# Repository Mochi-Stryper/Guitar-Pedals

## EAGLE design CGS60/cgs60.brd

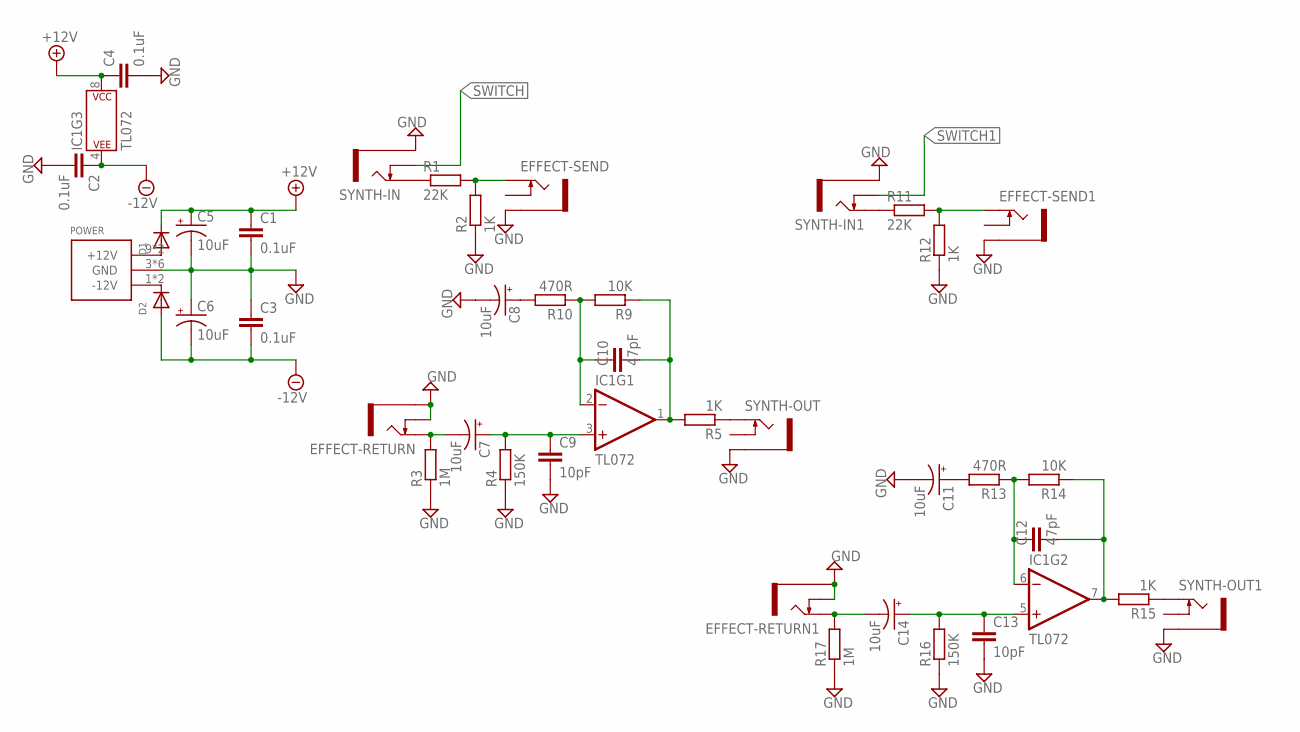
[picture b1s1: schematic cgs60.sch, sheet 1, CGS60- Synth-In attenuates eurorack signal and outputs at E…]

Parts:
C1, C2, C3, C4: 0.1uF; 0603
C5, C6, C7, C8, C11, C14: 10uF; PAN_B_SMD+THRU
C9, C13: 10pF; C0603
C10, C12: 47pF; C0603
D1, D2: DIODESOD-123; SOD-123
EFFECT-RETURN, EFFECT-RETURN1: THONKICONNNEW; WQP-PJ301M-12_JACK
EFFECT-SEND, EFFECT-SEND1: THONKICONNNEW; WQP-PJ301M-12_JACK
IC1: TL072; SO08
POWER: POWER_SIMPLE10; POWER_10
R1, R11: 22K; R0603
R2, R5, R12, R15: 1K; R0603
R3, R17: 1M; R0603
R4, R16: 150K; R0603
R9, R14: 10K; R0603
R10, R13: 470R; R0603
SYNTH-IN, SYNTH-IN1: THONKICONNNEW; WQP-PJ301M-12_JACK
SYNTH-OUT, SYNTH-OUT1: THONKICONNNEW; WQP-PJ301M-12_JACK

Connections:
+12V: C1.1, C4.1, C5.+, C5.++ (+), D1.C, IC1.8 (P$V+)
-12V: C2.1, C3.2, C6.-, C6.-- (-), D2.A, IC1.4 (P$V-)
GND: C1.2, C2.2, C3.1, C4.2, C5.-, C5.-- (-), C6.+, C6.++ (+), C8.-, C8.-- (-), C9.2, C11.-, C11.-- (-), C13.2, EFFECT-RETURN.P$2_SWITCH (SWITCH), EFFECT-RETURN.P$3_SLEEVE (SLEEVE), EFFECT-RETURN1.P$2_SWITCH (SWITCH), EFFECT-RETURN1.P$3_SLEEVE (SLEEVE), EFFECT-SEND.P$3_SLEEVE (SLEEVE), EFFECT-SEND1.P$3_SLEEVE (SLEEVE), POWER.3 (GND), POWER.4 (GND), POWER.5 (GND), POWER.6 (GND), POWER.7 (GND), POWER.8 (GND), R2.1, R3.1, R4.1, R12.1, R16.1, R17.1, SYNTH-IN.P$3_SLEEVE (SLEEVE), SYNTH-IN1.P$3_SLEEVE (SLEEVE), SYNTH-OUT.P$3_SLEEVE (SLEEVE), SYNTH-OUT1.P$3_SLEEVE (SLEEVE); also elsewhere on the board
unnamed: R1.1, SYNTH-IN.P$1_TIP (TIP)
unnamed: EFFECT-SEND.P$1_TIP (TIP), R1.2, R2.2
unnamed: C10.2, IC1.1 (OUT), R5.2, R9.1
unnamed: D1.A, POWER.9 (+12V), POWER.10 (+12V)
unnamed: C10.1, IC1.2 (-IN), R9.2, R10.1
unnamed: C8.+, C8.++ (+), R10.2
unnamed: C7.+, C7.++ (+), C9.1, IC1.3 (+IN), R4.2
unnamed: C7.-, C7.-- (-), EFFECT-RETURN.P$1_TIP (TIP), R3.2
unnamed: R5.1, SYNTH-OUT.P$1_TIP (TIP)
unnamed: R11.1, SYNTH-IN1.P$1_TIP (TIP)
unnamed: EFFECT-SEND1.P$1_TIP (TIP), R11.2, R12.2
unnamed: C11.+, C11.++ (+), R13.2
unnamed: C12.2, IC1.7 (OUT), R14.1, R15.2
unnamed: R15.1, SYNTH-OUT1.P$1_TIP (TIP)
unnamed: C14.-, C14.-- (-), EFFECT-RETURN1.P$1_TIP (TIP), R17.2
unnamed: C12.1, IC1.6 (-IN), R13.1, R14.2
unnamed: C13.1, C14.+, C14.++ (+), IC1.5 (+IN), R16.2
unnamed: D2.C, POWER.1 (-12V), POWER.2 (-12V)
SWITCH: SYNTH-IN.P$2_SWITCH (SWITCH); also elsewhere on the board
SWITCH1: SYNTH-IN1.P$2_SWITCH (SWITCH); also elsewhere on the board

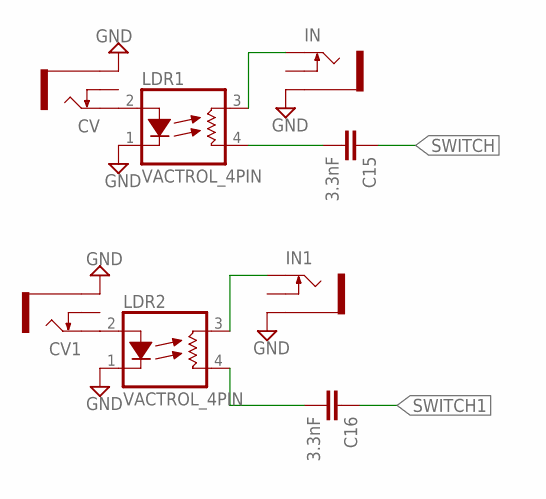
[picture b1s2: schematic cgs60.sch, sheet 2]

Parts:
C15, C16: 3.3nF; 0603
CV, CV1: THONKICONNNEW; WQP-PJ301M-12_JACK
IN, IN1: THONKICONNNEW; WQP-PJ301M-12_JACK
LDR1, LDR2: VACTROL_4PIN; VACTROL_4PIN_VTL5C

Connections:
GND: CV.P$3_SLEEVE (SLEEVE), CV1.P$3_SLEEVE (SLEEVE), IN.P$3_SLEEVE (SLEEVE), IN1.P$3_SLEEVE (SLEEVE), LDR1.1 (LED-), LDR2.1 (LED-); also elsewhere on the board
unnamed: CV.P$1_TIP (TIP), LDR1.2 (LED+)
unnamed: IN.P$1_TIP (TIP), LDR1.3 (RES1)
unnamed: C15.2, LDR1.4 (RES2)
unnamed: CV1.P$1_TIP (TIP), LDR2.2 (LED+)
unnamed: IN1.P$1_TIP (TIP), LDR2.3 (RES1)
unnamed: C16.2, LDR2.4 (RES2)
SWITCH: C15.1; also elsewhere on the board
SWITCH1: C16.1; also elsewhere on the board

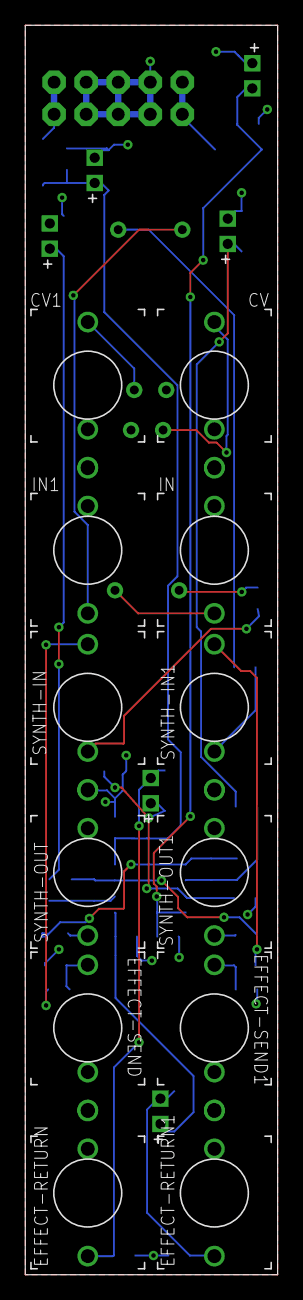
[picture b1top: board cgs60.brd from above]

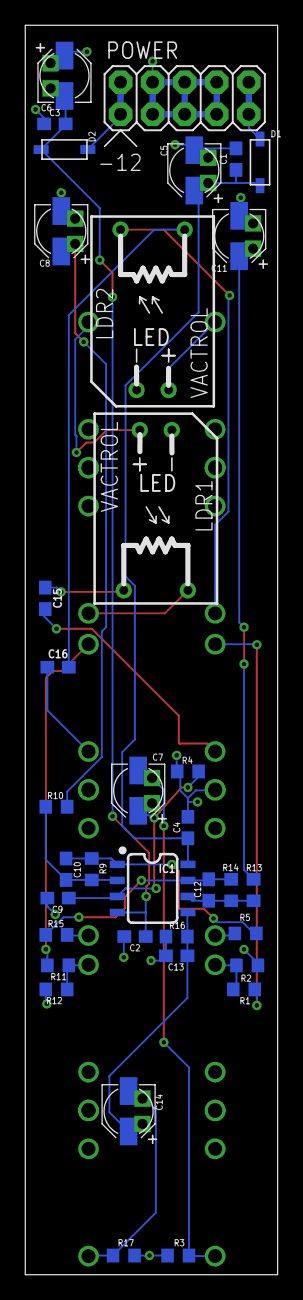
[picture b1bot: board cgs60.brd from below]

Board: 2 copper layers, 20.0 x 99.0 mm, 48 parts (36 on the bottom side), 29 nets.

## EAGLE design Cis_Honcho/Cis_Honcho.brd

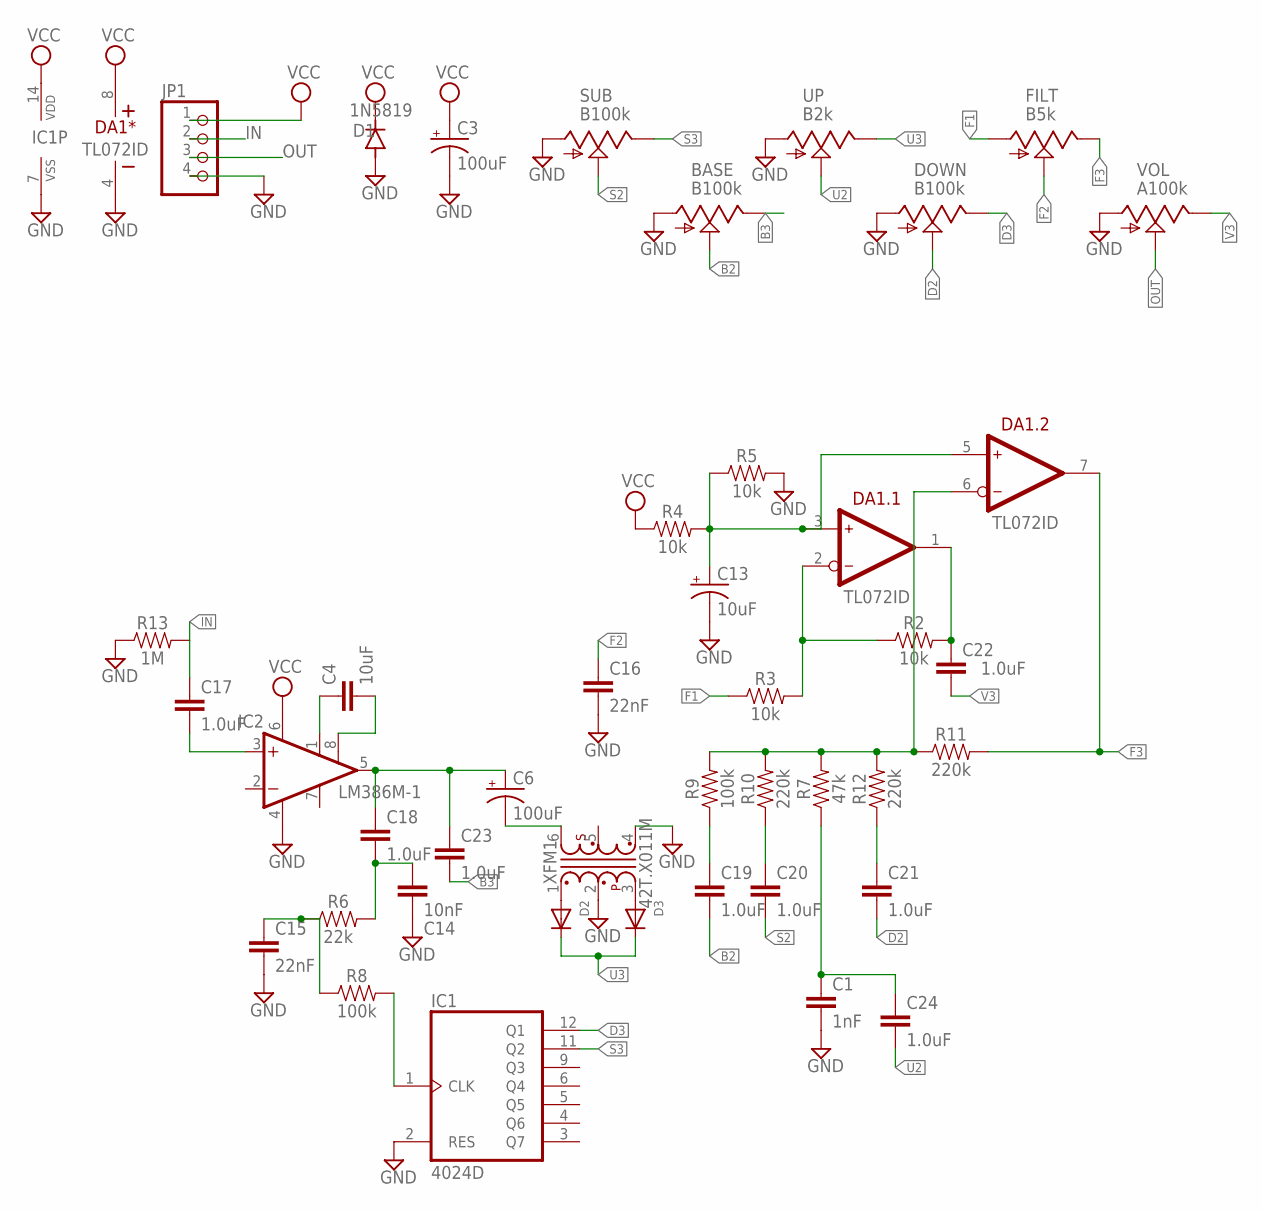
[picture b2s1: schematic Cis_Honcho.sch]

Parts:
BASE: B100k; 9MM_SNAP-IN_POT
C1: 1nF; 0603
C3, C6: 100uF; E2,5-6
C4: 10uF; 1210
C13: 10uF; PANASONIC_B
C14: 10nF; 0603
C15, C16: 22nF; 0603
C17, C18, C19, C20, C21, C22, C23, C24: 1.0uF; 0603
D1: 1N5819; SOD123
D2, D3: DIODESOD-123; SOD-123
DA1: TL072ID; SO-8
DOWN: B100k; 9MM_SNAP-IN_POT
FILT: B5k; 9MM_SNAP-IN_POT
IC1: 4024D; SO14
IC2: LM386M-1; SO08
JP1: PINHD-1X4; 1X04
R2, R3, R4, R5: 10k; 0603
R6: 22k; 0603
R7: 47k; 0603
R8, R9: 100k; 0603
R10, R11, R12: 220k; 0603
R13: 1M; 0603
SUB: B100k; 9MM_SNAP-IN_POT
UP: B2k; 9MM_SNAP-IN_POT
VOL: A100k; 9MM_SNAP-IN_POT
XFM1: 42T.X011M; 42TM

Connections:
B2: BASE.2 (S), C19.2
B3: BASE.3 (E), C23.2
D2: C21.2, DOWN.2 (S)
D3: DOWN.3 (E), IC1.12 (Q1)
F1: FILT.1 (A), R3.1
F2: C16.1, FILT.2 (S)
F3: DA1.7 (OUT), FILT.3 (E), R11.2
GND: BASE.1 (A), C1.2, C3.-, C13.-, C14.2, C15.2, C16.2, D1.A, DA1.4 (V-), DOWN.1 (A), IC1.2 (RES), IC1.7 (VSS), IC2.4 (GND), JP1.4, R5.2, R13.1, SUB.1 (A), UP.1 (A), VOL.1 (A), XFM1.2, XFM1.4
IN: C17.1, JP1.2, R13.2
unnamed: C17.2, IC2.3 (+IN)
unnamed: C4.1, IC2.1 (GAIN)
unnamed: C4.2, IC2.8 (GAIN)
unnamed: C6.+, C18.1, C23.1, IC2.5 (OUT)
unnamed: C14.1, C18.2, R6.2
unnamed: C15.1, R6.1, R8.1
unnamed: IC1.1 (CLK), R8.2
unnamed: C6.-, XFM1.6
unnamed: D2.A, XFM1.1
unnamed: D3.A, XFM1.3
unnamed: DA1.6 (IN-), R7.2, R9.2, R10.2, R11.1, R12.2
unnamed: C19.1, R9.1
unnamed: C20.1, R10.1
unnamed: C21.1, R12.1
unnamed: C1.1, C24.1, R7.1
unnamed: C13.+, DA1.3 (IN+), DA1.5 (IN+), R4.2, R5.1
unnamed: C22.1, DA1.1 (OUT), R2.2
unnamed: DA1.2 (IN-), R2.1, R3.2
OUT: JP1.3, VOL.2 (S)
S2: C20.2, SUB.2 (S)
S3: IC1.11 (Q2), SUB.3 (E)
U2: C24.2, UP.2 (S)
U3: D2.C, D3.C, UP.3 (E)
V3: C22.2, VOL.3 (E)
VCC: C3.+, D1.C, DA1.8 (V+), IC1.14 (VDD), IC2.6 (VS), JP1.1, R4.1

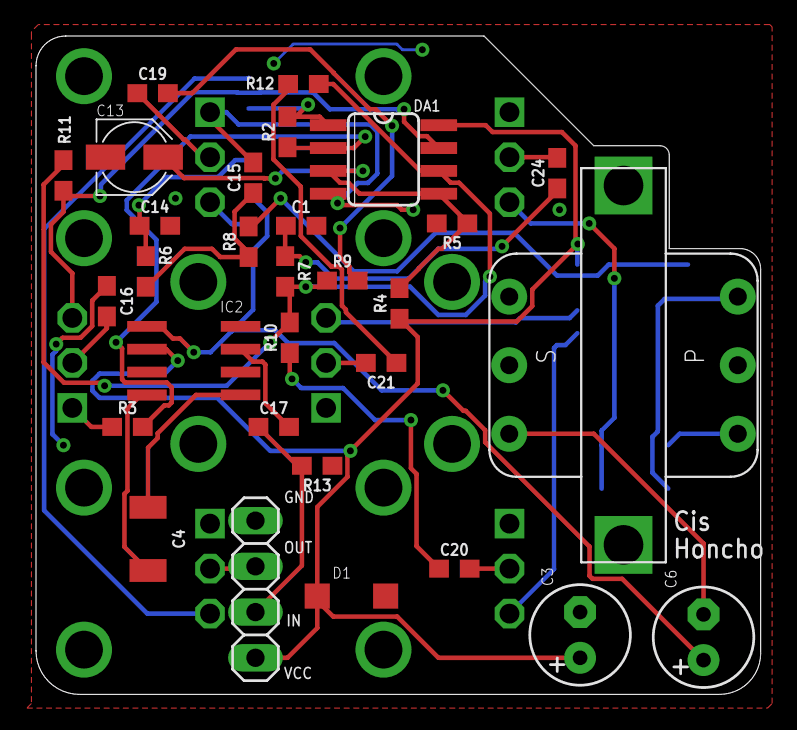
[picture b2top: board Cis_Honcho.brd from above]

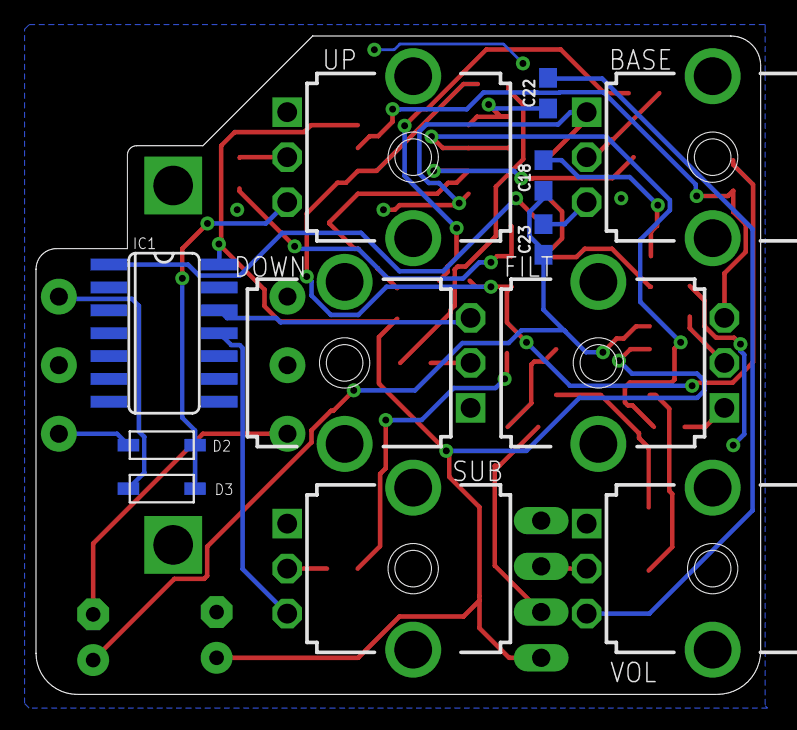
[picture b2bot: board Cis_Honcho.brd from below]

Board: 2 copper layers, 40.3 x 36.6 mm, 42 parts (12 on the bottom side), 34 nets.

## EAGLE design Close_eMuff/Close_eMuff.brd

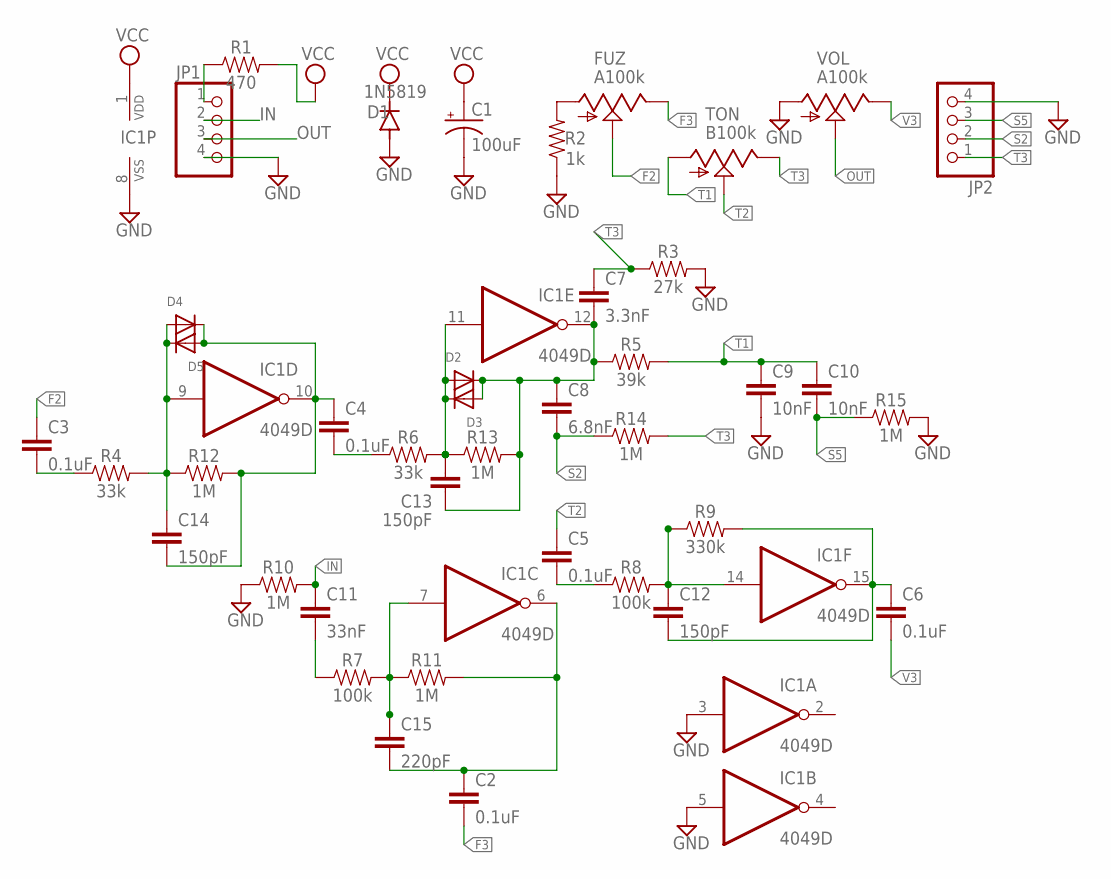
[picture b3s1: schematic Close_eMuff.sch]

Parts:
C1: 100uF; PAN_B_SMD+THRU
C2, C3, C4, C5, C6: 0.1uF; 0603
C7: 3.3nF; 0603
C8: 6.8nF; 0603
C9, C10: 10nF; 0603
C11: 33nF; 0603
C12, C13, C14: 150pF; 0603
C15: 220pF; 0603
D1: 1N5819; SOD123
D2, D3, D4, D5: DIODESOD-123; SOD-123
FUZ: A100k; 9MM_SNAP-IN_POT
IC1: 4049D; SO16
JP1, JP2: PINHD-1X4; 1X04
R1: 470; 0603
R2: 1k; 0603
R3: 27k; 0603
R4, R6: 33k; 0603
R5: 39k; 0603
R7, R8: 100k; 0603
R9: 330k; 0603
R10, R11, R12, R13, R14, R15: 1M; 0603
TON: B100k; 9MM_SNAP-IN_POT
VOL: A100k; 9MM_SNAP-IN_POT

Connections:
F2: C3.1, FUZ.2 (S)
F3: C2.2, FUZ.3 (E)
GND: C1.-, C1.-- (-), C9.2, D1.A, IC1.3 (I), IC1.5 (I), IC1.8 (VSS), JP1.4, JP2.4, R2.1, R3.2, R10.1, R15.2, VOL.1 (A)
IN: C11.1, JP1.2, R10.2
unnamed: C11.2, R7.1
unnamed: C15.1, IC1.7 (I), R7.2, R11.1
unnamed: FUZ.1 (A), R2.2
unnamed: C2.1, C15.2, IC1.6 (O), R11.2
unnamed: C3.2, R4.1
unnamed: C14.1, D4.A, D5.C, IC1.9 (I), R4.2, R12.1
unnamed: C4.2, R6.1
unnamed: C4.1, C14.2, D4.C, D5.A, IC1.10 (O), R12.2
unnamed: C13.1, D2.A, D3.C, IC1.11 (I), R6.2, R13.1
unnamed: JP1.1, R1.1
unnamed: C5.2, R8.1
unnamed: C7.2, C8.1, C13.2, D2.C, D3.A, IC1.12 (O), R5.1, R13.2
unnamed: C12.1, IC1.14 (I), R8.2, R9.1
unnamed: C6.1, C12.2, IC1.15 (O), R9.2
OUT: JP1.3, VOL.2 (S)
S2: C8.2, JP2.2, R14.1
S5: C10.2, JP2.3, R15.1
T1: C9.1, C10.1, R5.2, TON.1 (A)
T2: C5.1, TON.2 (S)
T3: C7.1, JP2.1, R3.1, R14.2, TON.3 (E)
V3: C6.2, VOL.3 (E)
VCC: C1.+, C1.++ (+), D1.C, IC1.1 (VDD), R1.2

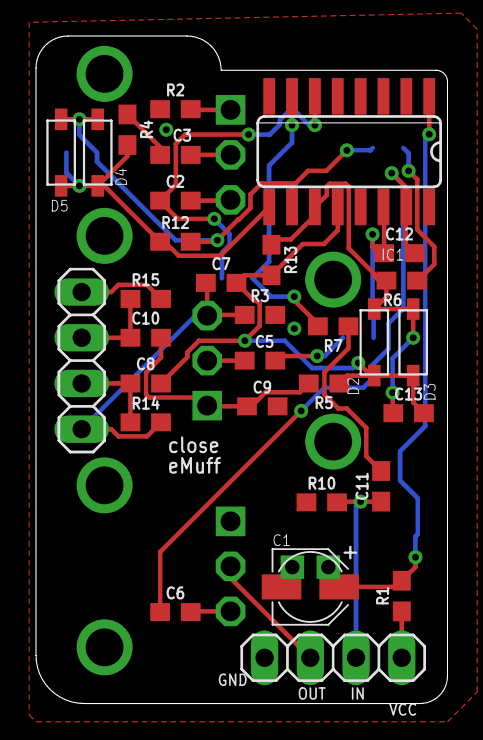
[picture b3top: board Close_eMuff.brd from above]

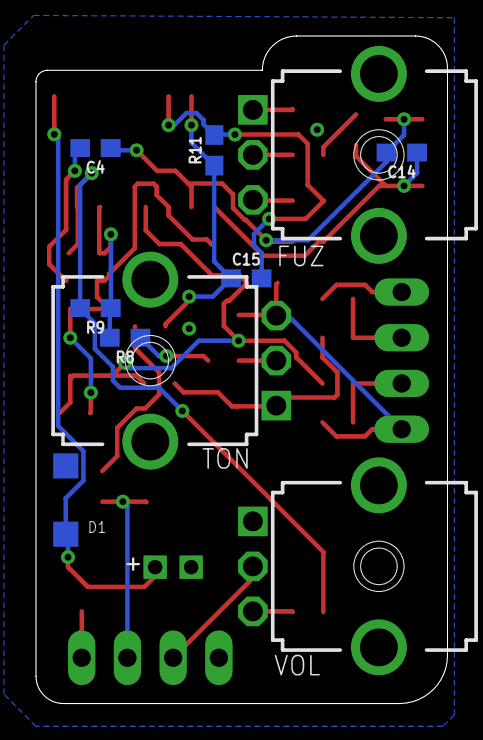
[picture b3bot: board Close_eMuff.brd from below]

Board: 2 copper layers, 22.9 x 37.1 mm, 41 parts (10 on the bottom side), 26 nets.

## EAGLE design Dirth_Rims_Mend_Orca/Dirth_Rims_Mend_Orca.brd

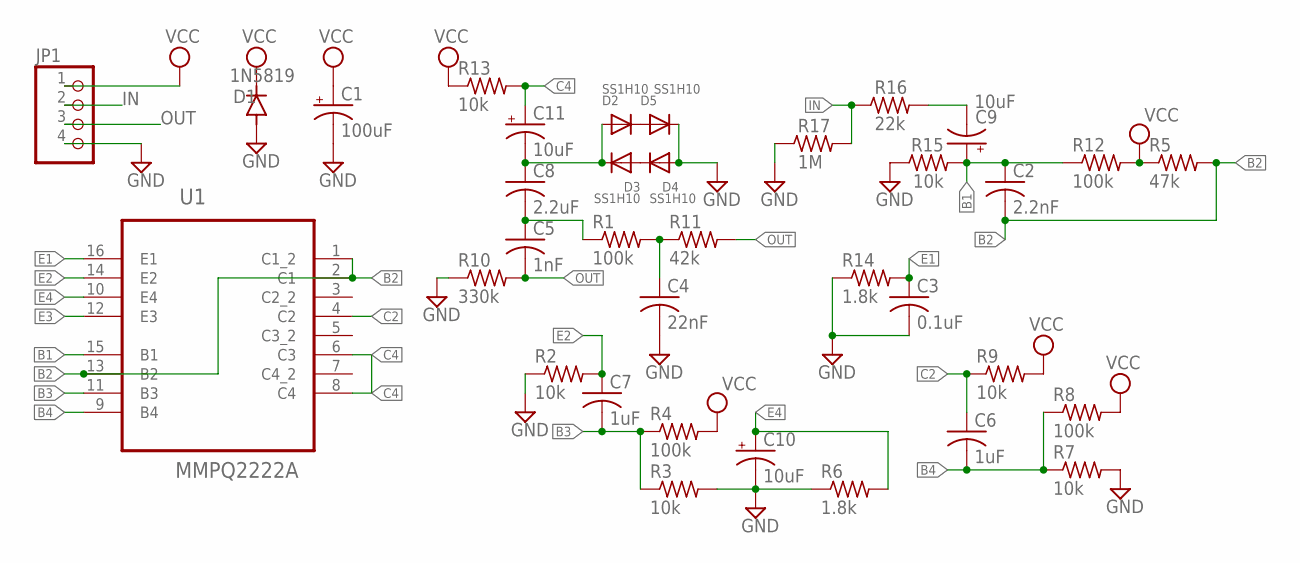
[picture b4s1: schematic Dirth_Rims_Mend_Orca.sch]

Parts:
C1: 100uF; PAN_B_SMD+THRU
C2: 2.2nF; C0603
C3: 0.1uF; C0603
C4: 22nF; C0603
C5: 1nF; C0603
C6, C7: 1uF; C0603
C8: 2.2uF; C0603
C9, C10, C11: 10uF; PAN_B_SMD+THRU
D1: 1N5819; SOD123
D2, D3, D4, D5: SS1H10; SMADIODE
JP1: PINHD-1X4; 1X04
R1, R4, R8, R12: 100k; R0603
R2, R3, R7, R9, R13, R15: 10k; R0603
R5: 47k; R0603
R6, R14: 1.8k; R0603
R10: 330k; R0603
R11: 42k; R0603
R16: 22k; R0603
R17: 1M; R0603
U1: MMPQ2222A; SOIC127P600X175-16N

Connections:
B1: C2.1, C9.+, C9.++ (+), R12.1, R15.2, U1.15 (B1)
B2: C2.2, R5.2, U1.1 (C1_2), U1.2 (C1), U1.13 (B2)
B3: C7.2, R3.1, R4.1, U1.11 (B3)
B4: C6.2, R7.1, R8.1, U1.9 (B4)
C2: C6.1, R9.1, U1.4 (C2)
C4: C11.+, C11.++ (+), R13.2, U1.6 (C3), U1.8 (C4)
E1: C3.1, R14.2, U1.16 (E1)
E2: C7.1, R2.2, U1.14 (E2)
E3: U1.12 (E3)
E4: C10.+, C10.++ (+), R6.2, U1.10 (E4)
GND: C1.-, C1.-- (-), C3.2, C4.2, C10.-, C10.-- (-), D1.A, D4.A, D5.C, JP1.4, R2.1, R3.2, R6.1, R7.2, R10.1, R14.1, R15.1, R17.1
IN: JP1.2, R16.1, R17.2
unnamed: C9.-, C9.-- (-), R16.2
unnamed: C8.1, C11.-, C11.-- (-), D2.A, D3.C
unnamed: C5.1, C8.2, R1.1
unnamed: D3.A, D4.C
unnamed: D2.C, D5.A
unnamed: C4.1, R1.2, R11.1
OUT: C5.2, JP1.3, R10.2, R11.2
VCC: C1.+, C1.++ (+), D1.C, JP1.1, R4.2, R5.1, R8.2, R9.2, R12.2, R13.1

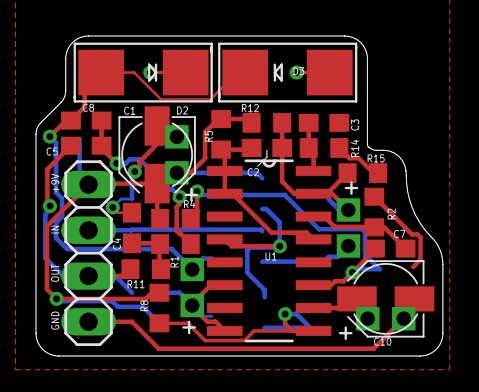
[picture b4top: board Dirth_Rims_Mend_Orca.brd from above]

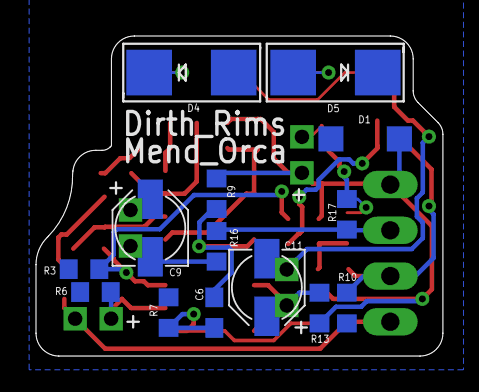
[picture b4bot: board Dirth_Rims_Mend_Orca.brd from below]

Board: 2 copper layers, 22.6 x 17.8 mm, 35 parts (14 on the bottom side), 19 nets.

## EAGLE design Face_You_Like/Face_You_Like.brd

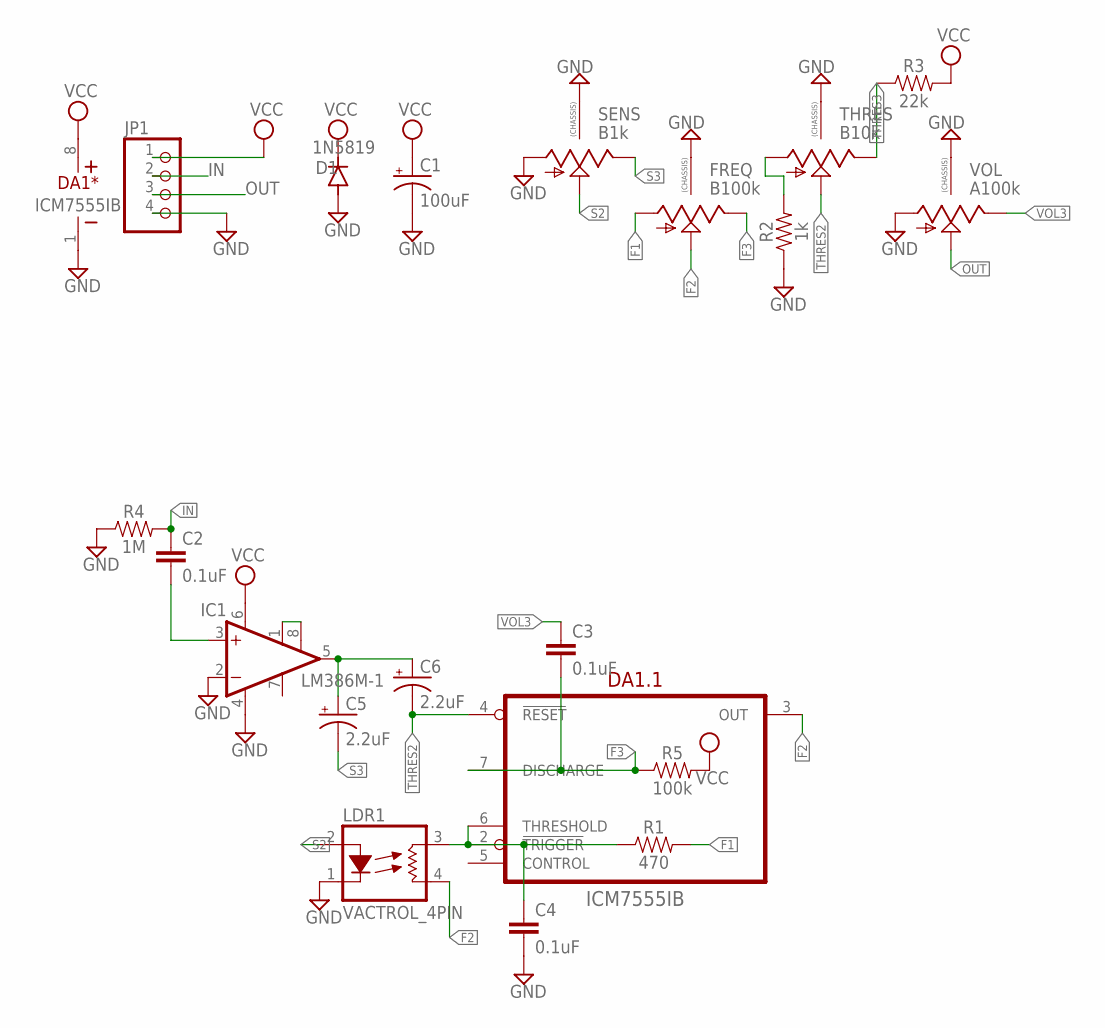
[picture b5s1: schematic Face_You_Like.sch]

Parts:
C1: 100uF; PAN_B_SMD+THRU
C2, C3, C4: 0.1uF; 0603
C5, C6: 2.2uF; PAN_B_SMD+THRU
D1: 1N5819; SOD123
DA1: ICM7555IB; SO-8
FREQ: B100k; 9MM_SNAP-IN_POT
IC1: LM386M-1; SO08
JP1: PINHD-1X4; 1X04
LDR1: VACTROL_4PIN; VACTROL_4PIN_VTL5C
R1: 470; 0603
R2: 1k; 0603
R3: 22k; 0603
R4: 1M; 0603
R5: 100k; 0603
SENS: B1k; 9MM_SNAP-IN_POT
THRES: B10k; 9MM_SNAP-IN_POT
VOL: A100k; 9MM_SNAP-IN_POT

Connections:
F1: FREQ.1 (A), R1.2
F2: DA1.3 (OUT), FREQ.2 (S), LDR1.4 (RES2)
F3: C3.2, DA1.7 (DISCHARGE), FREQ.3 (E), R5.1
GND: C1.-, C1.-- (-), C4.2, D1.A, DA1.1 (V-), FREQ.CHASSIS1, FREQ.CHASSIS2, IC1.2 (-IN), IC1.4 (GND), JP1.4, LDR1.1 (LED-), R2.1, R4.1, SENS.1 (A), SENS.CHASSIS1, SENS.CHASSIS2, THRES.CHASSIS1, THRES.CHASSIS2, VOL.1 (A), VOL.CHASSIS1, VOL.CHASSIS2
IN: C2.1, JP1.2, R4.2
unnamed: IC1.1 (GAIN), IC1.8 (GAIN)
unnamed: C2.2, IC1.3 (+IN)
unnamed: R2.2, THRES.1 (A)
unnamed: C5.+, C5.++ (+), C6.+, C6.++ (+), IC1.5 (OUT)
unnamed: C4.1, DA1.2 (!TRIGGER), DA1.6 (THRESHOLD), LDR1.3 (RES1), R1.1
OUT: JP1.3, VOL.2 (S)
S2: LDR1.2 (LED+), SENS.2 (S)
S3: C5.-, C5.-- (-), SENS.3 (E)
THRES2: C6.-, C6.-- (-), DA1.4 (!RESET), THRES.2 (S)
THRES3: R3.1, THRES.3 (E)
VCC: C1.+, C1.++ (+), D1.C, DA1.8 (V+), IC1.6 (VS), JP1.1, R3.2, R5.2
VOL3: C3.1, VOL.3 (E)

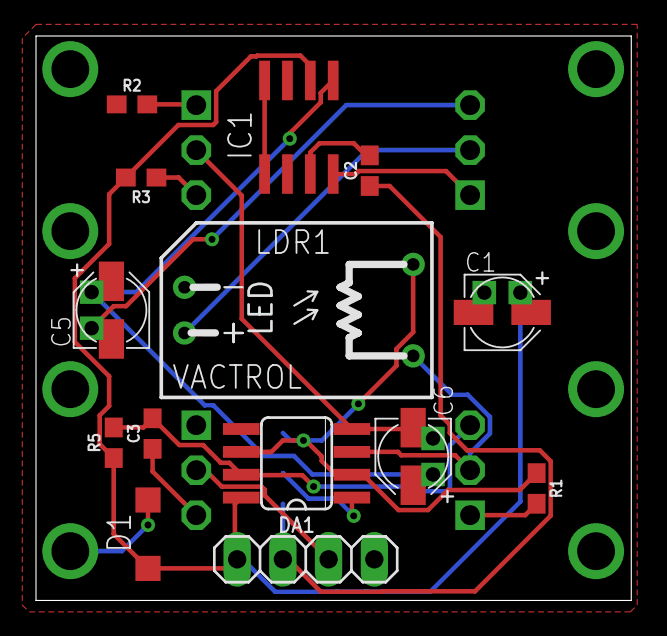
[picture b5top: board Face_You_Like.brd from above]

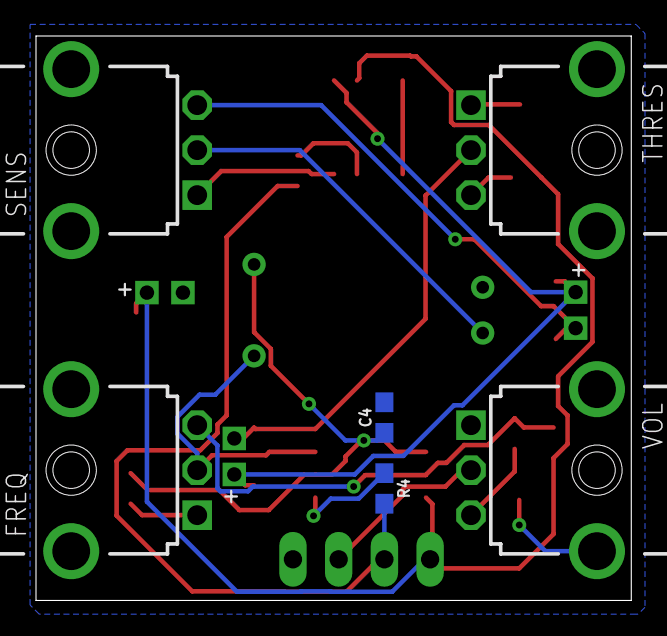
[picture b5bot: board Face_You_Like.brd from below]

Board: 2 copper layers, 33.1 x 31.4 mm, 20 parts (6 on the bottom side), 17 nets.

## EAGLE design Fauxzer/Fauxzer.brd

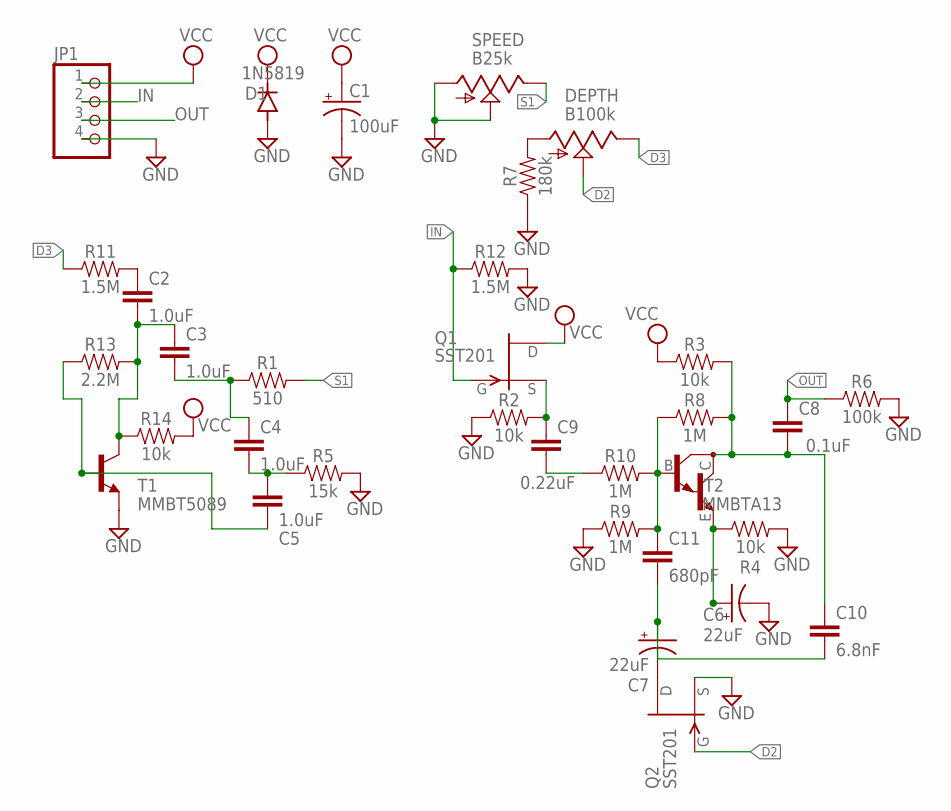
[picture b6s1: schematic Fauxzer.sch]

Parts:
C1: 100uF; PAN_B_SMD+THRU
C2, C3, C4, C5: 1.0uF; 0805
C6, C7: 22uF; PAN_B_SMD+THRU
C8: 0.1uF; 0603
C9: 0.22uF; 0603
C10: 6.8nF; 0603
C11: 680pF; 0603
D1: 1N5819; SOD123
DEPTH: B100k; 9MM_SNAP-IN_POT
JP1: PINHD-1X4; 1X04
Q1, Q2: SST201; SOT23
R1: 510; 0603
R2, R3, R4, R14: 10k; 0603
R5: 15k; 0603
R6: 100k; 0603
R7: 180k; 0603
R8, R9, R10: 1M; 0603
R11, R12: 1.5M; 0603
R13: 2.2M; 0603
SPEED: B25k; 9MM_SNAP-IN_POT
T1: MMBT5089; SOT23-BEC
T2: MMBTA13; SOT23-BEC

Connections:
D2: DEPTH.2 (S), Q2.3 (G)
D3: DEPTH.3 (E), R11.1
GND: C1.-, C1.-- (-), C6.-, C6.-- (-), D1.A, JP1.4, Q2.2 (S), R2.1, R4.2, R5.2, R6.2, R7.1, R9.1, R12.2, SPEED.1 (A), SPEED.2 (S), T1.E
IN: JP1.2, Q1.3 (G), R12.1
unnamed: C2.1, R11.2
unnamed: C9.1, Q1.2 (S), R2.2
unnamed: C9.2, R10.1
unnamed: C11.1, R8.1, R9.2, R10.2, T2.B
unnamed: C7.+, C7.++ (+), C10.2, C11.2
unnamed: C7.-, C7.-- (-), Q2.1 (D)
unnamed: C8.2, C10.1, R3.2, R8.2, T2.C
unnamed: C6.+, C6.++ (+), R4.1, T2.E
unnamed: DEPTH.1 (A), R7.2
unnamed: C3.2, C4.1, R1.1
unnamed: C2.2, C3.1, R13.2, R14.1, T1.C
unnamed: C5.2, R13.1, T1.B
unnamed: C4.2, C5.1, R5.1
OUT: C8.1, JP1.3, R6.1
S1: R1.2, SPEED.3 (E)
VCC: C1.+, C1.++ (+), D1.C, JP1.1, Q1.1 (D), R3.1, R14.2

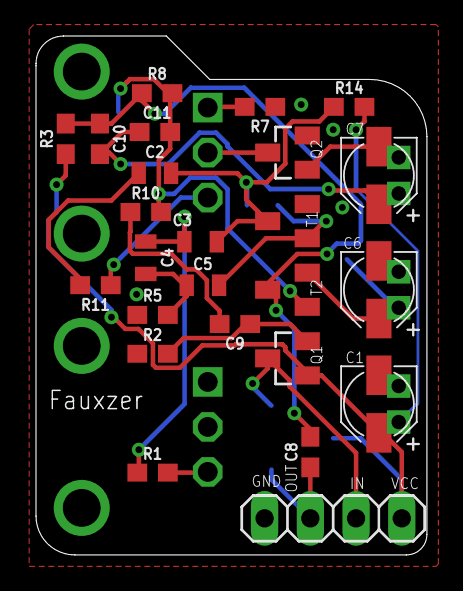
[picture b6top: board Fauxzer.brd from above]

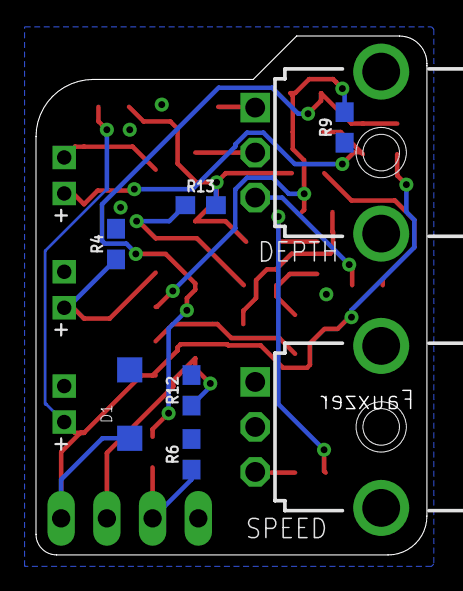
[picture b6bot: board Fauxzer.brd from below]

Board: 2 copper layers, 21.7 x 28.8 mm, 33 parts (8 on the bottom side), 20 nets.

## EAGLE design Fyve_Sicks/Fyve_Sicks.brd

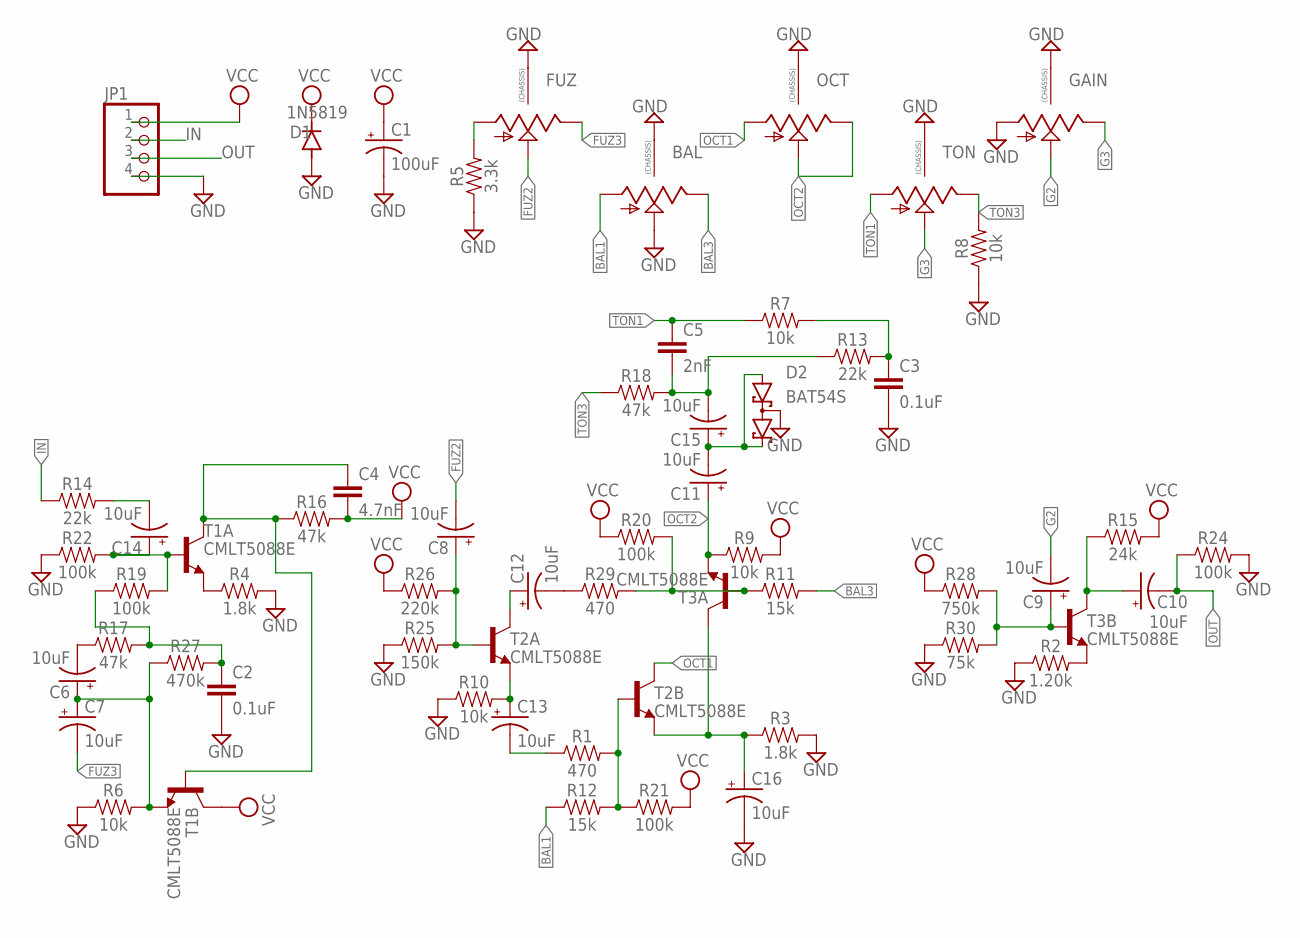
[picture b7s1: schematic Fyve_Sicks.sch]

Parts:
BAL: 9MM_SNAP-IN_POT_CHASSIS; 9MM_SNAP-IN_POT
C1: 100uF; PAN_B_SMD+THRU
C2, C3: 0.1uF; 0603
C4: 4.7nF; 0603
C5: 2nF; 0603
C6, C7, C8, C9, C10, C11, C12, C13, C14, C15, C16: 10uF; EIA3528
D1: 1N5819; SOD123
D2: BAT54S; SOT23
FUZ: 9MM_SNAP-IN_POT_CHASSIS; 9MM_SNAP-IN_POT
GAIN: 9MM_SNAP-IN_POT_CHASSIS; 9MM_SNAP-IN_POT
JP1: PINHD-1X4; 1X04
OCT: 9MM_SNAP-IN_POT_CHASSIS; 9MM_SNAP-IN_POT
R1, R29: 470; 0603
R2: 1.20k; 0603
R3, R4: 1.8k; 0603
R5: 3.3k; 0603
R6, R7, R8, R9, R10: 10k; 0603
R11, R12: 15k; 0603
R13, R14: 22k; 0603
R15: 24k; 0603
R16, R17, R18: 47k; 0603
R19, R20, R21, R22, R24: 100k; 0603
R25: 150k; 0603
R26: 220k; 0603
R27: 470k; 0603
R28: 750k; 0603
R30: 75k; 0603
T1, T2, T3: CMLT5088E; SOT563
TON: 9MM_SNAP-IN_POT_CHASSIS; 9MM_SNAP-IN_POT

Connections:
BAL1: BAL.1 (A), R12.1
BAL3: BAL.3 (E), R11.2
FUZ2: C8.C (-), FUZ.2 (S)
FUZ3: C7.C (-), FUZ.3 (E)
G2: C9.C (-), GAIN.2 (S)
G3: GAIN.3 (E), TON.2 (S)
GND: BAL.2 (S), BAL.CHASSIS1, BAL.CHASSIS2, C1.-, C1.-- (-), C2.2, C3.2, C16.C (-), D1.A, D2.3 (C1A2), FUZ.CHASSIS1, FUZ.CHASSIS2, GAIN.1 (A), GAIN.CHASSIS1, GAIN.CHASSIS2, JP1.4, OCT.CHASSIS1, OCT.CHASSIS2, R2.1, R3.2, R4.2, R5.1, R6.1, R8.1, R10.1, R22.1, R24.2, R25.1, R30.1, TON.CHASSIS1, TON.CHASSIS2
IN: JP1.2, R14.1
unnamed: FUZ.1 (A), R5.2
unnamed: C13.C (-), R1.1
unnamed: C2.1, R17.2, R19.1, R27.2
unnamed: R1.2, R12.2, R21.1, T2.5 (B)
unnamed: R11.1, R20.2, R29.2, T3.2 (B)
unnamed: C12.C (-), R29.1
unnamed: C12.A (+), T2.6 (C)
unnamed: C11.C (-), C15.A (+), D2.1 (A1), D2.2 (C2)
unnamed: C5.2, C15.C (-), R13.1, R18.2
unnamed: C3.1, R7.2, R13.2
unnamed: C9.A (+), R28.2, R30.2, T3.5 (B)
unnamed: R2.2, T3.4 (E)
unnamed: C10.A (+), R15.1, T3.3 (C)
unnamed: C6.A (+), C7.A (+), R6.2, R27.1, T1.4 (E)
unnamed: C14.C (-), R14.2
unnamed: C14.A (+), R19.2, R22.2, T1.2 (B)
unnamed: C6.C (-), R17.1
unnamed: C8.A (+), R25.2, R26.2, T2.2 (B)
unnamed: R4.1, T1.1 (E)
unnamed: C13.A (+), R10.2, T2.1 (E)
unnamed: C4.1, R16.1, T1.5 (B), T1.6 (C)
unnamed: C16.A (+), R3.1, T2.4 (E), T3.6 (C)
OCT1: OCT.1 (A), T2.3 (C)
OCT2: C11.A (+), OCT.2 (S), OCT.3 (E), R9.1, T3.1 (E)
OUT: C10.C (-), JP1.3, R24.1
TON1: C5.1, R7.1, TON.1 (A)
TON3: R8.2, R18.1, TON.3 (E)
VCC: C1.+, C1.++ (+), C4.2, D1.C, JP1.1, R9.2, R15.2, R16.2, R20.1, R21.2, R26.1, R28.1, T1.3 (C)

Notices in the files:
parts and their libraries:
SparkFun-Capacitors: Licensing: Creative Commons ShareAlike 4.0 International - https://creativecommons.org/licenses/by-sa/4.0
